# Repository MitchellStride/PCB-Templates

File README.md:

# PCB-Templates
Useful blank PCB schematics &amp; layouts saved from previous projects. e.g. BeagleBone Black Cape, Arduino Shield.

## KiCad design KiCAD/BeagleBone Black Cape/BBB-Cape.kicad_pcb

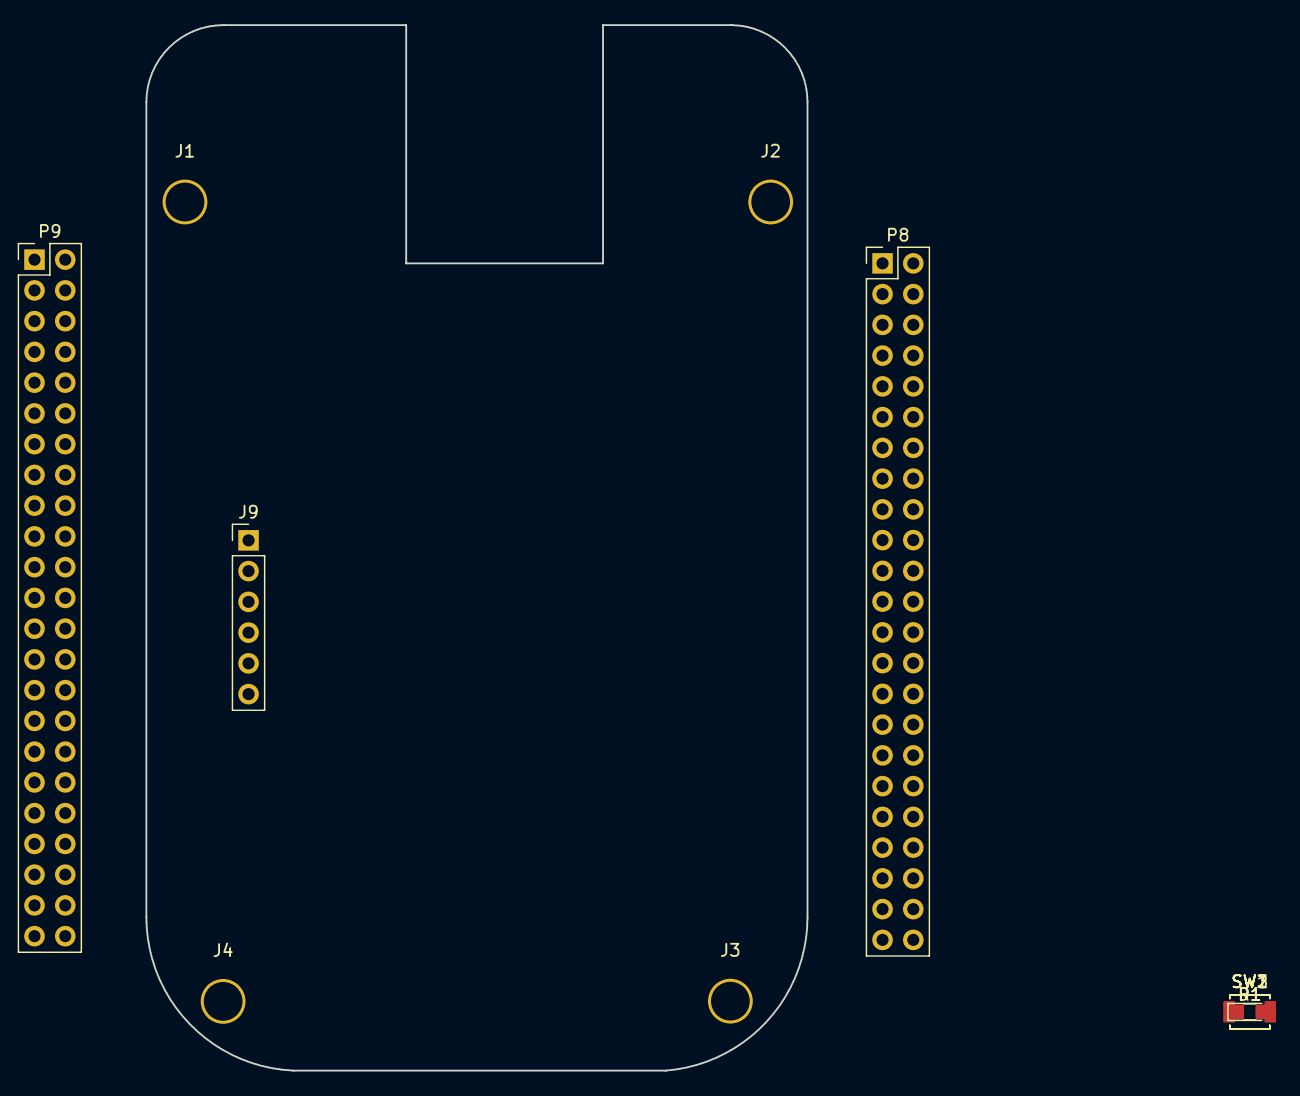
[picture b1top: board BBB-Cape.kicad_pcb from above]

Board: 2 copper layers, 54.6 x 86.4 mm, 12 parts (0 on the bottom side), 9 nets, no tracks yet.

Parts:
D1: LED; LED_0805
J1, J2, J3, J4: MOUNTING_HOLE; MountingHole_3.2mm_M3_Pad
J9: 01x06_Stackable Header; Pin_Header_Straight_1x06_Pitch2.54mm
P8, P9: 02x23_Stackable Header; Pin_Header_Straight_2x23_Pitch2.54mm
R1: 330; R_0603
SW1: W5500_RST; SW_SPST_B3U-1000P
SW2: SYS_RST; SW_SPST_B3U-1000P
SW3: Power; SW_SPST_B3U-1000P

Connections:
DGND: J1.1, J2.1, J3.1, J4.1, P8.1, P8.2, P9.1, P9.2, P9.43, P9.44, P9.45, P9.46, R1.2, SW1.2, SW2.2, SW3.2
EHRPWM2A: P8.19, P8.45
EHRPWM2B: P8.13, P8.46
unnamed: D1.1, R1.1
PWR_BUT: P9.9, SW3.1
SYS_5V: P9.7, P9.8
SYS_RESETn: P9.10, SW2.1
VDD_3V3: D1.2, P9.3, P9.4
VDD_5V: P9.5, P9.6

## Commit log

2018-01-16 added blank uno shield template
2018-01-16 BeagleBone Updated, headers need to be moved into proper spot
2018-01-16 BeagleBone previous project files deleted.
2018-02-07 added kicad repos again
